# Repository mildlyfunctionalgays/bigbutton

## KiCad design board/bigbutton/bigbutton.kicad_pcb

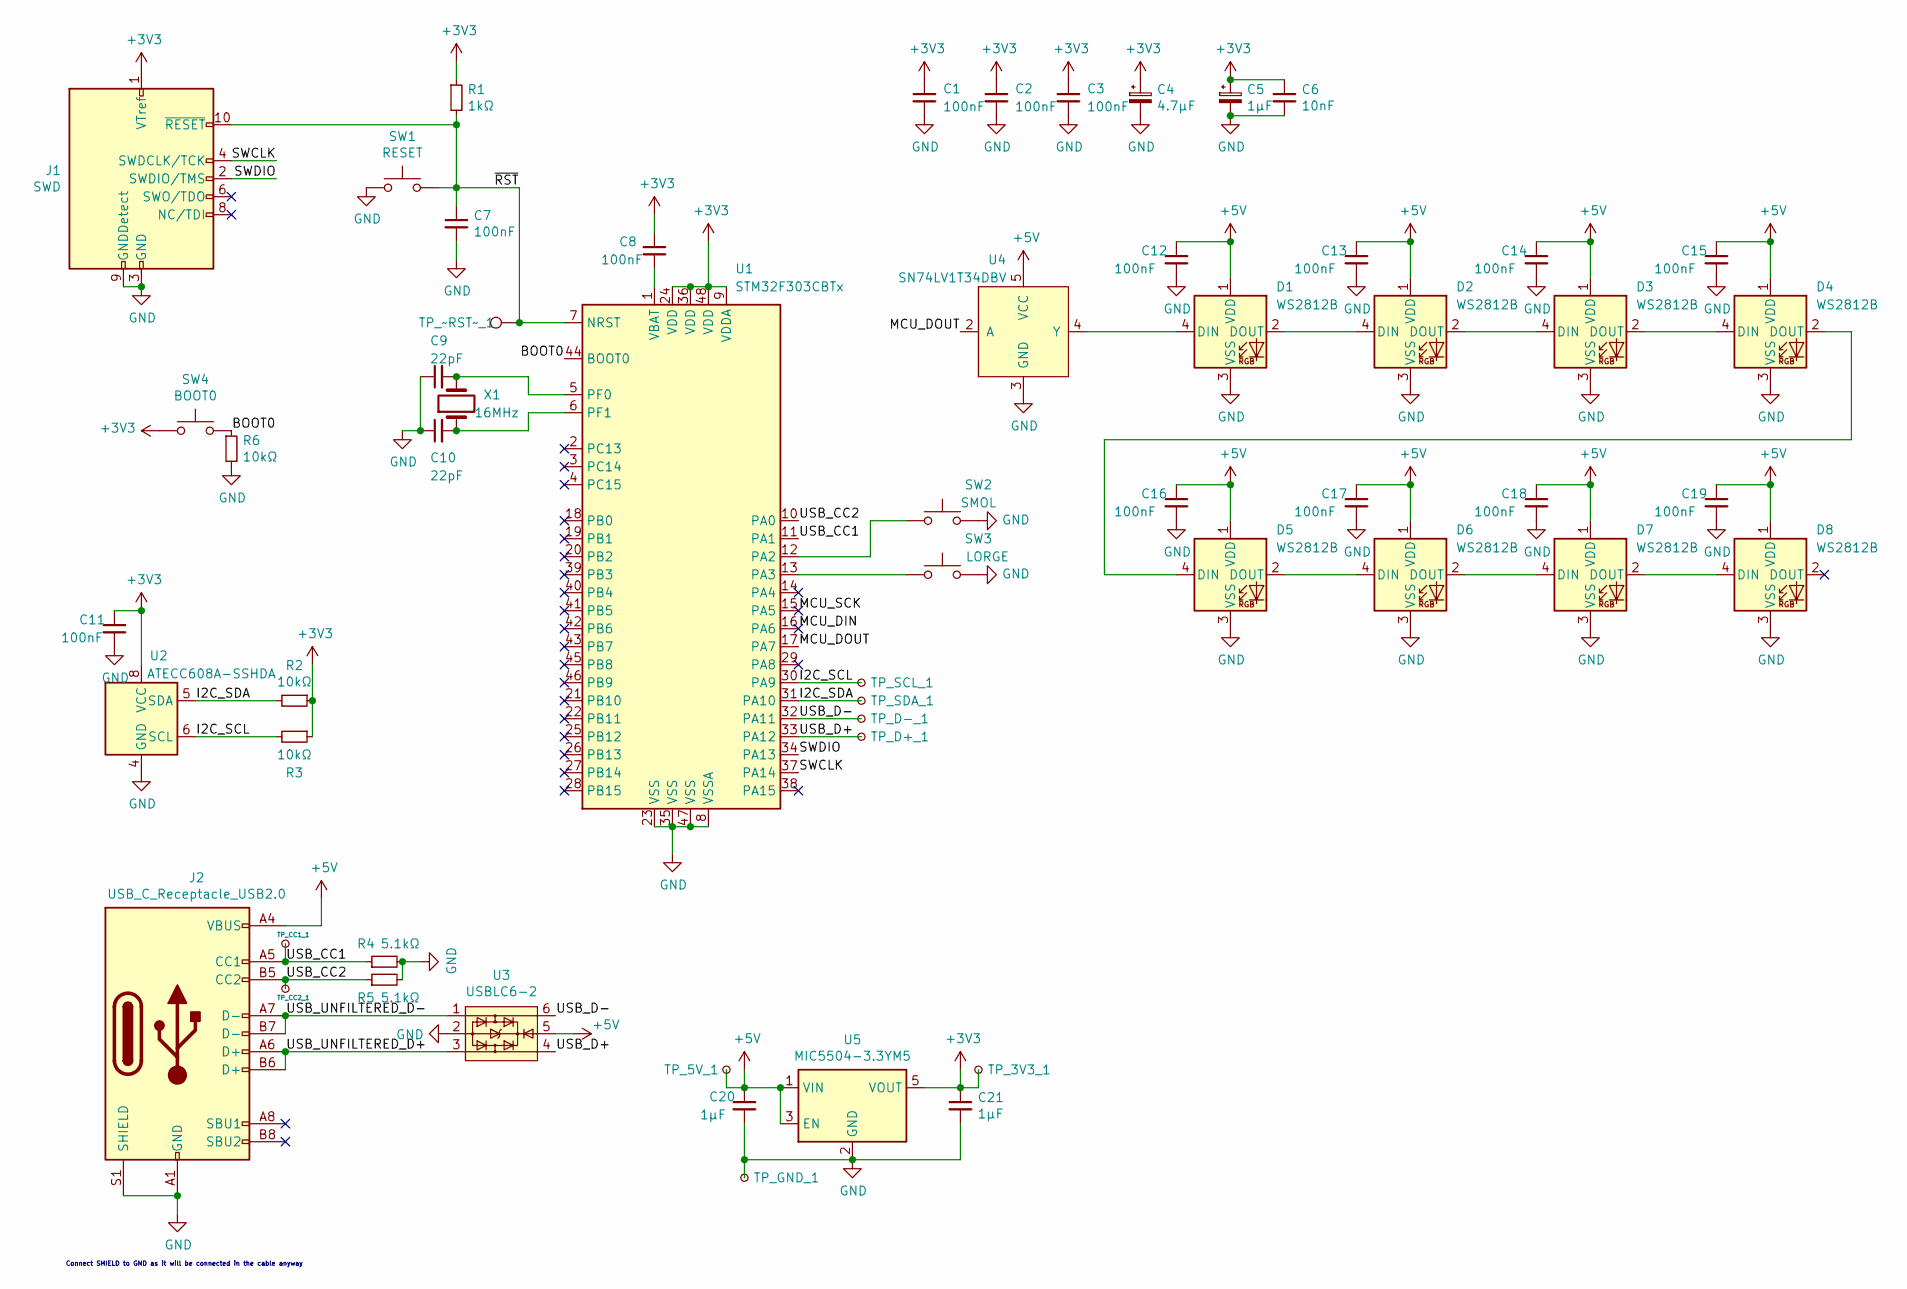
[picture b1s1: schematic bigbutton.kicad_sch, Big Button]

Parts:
C1, C2, C3, C7, C8, C11, C12, C13, C14, C15, C16, C17, C18, C19: 100nF; C_0603_1608Metric
C4: 4.7µF; C_0603_1608Metric
C5, C20, C21: 1µF; C_0603_1608Metric
C6: 10nF; C_0603_1608Metric
C9, C10: 22pF; C_0603_1608Metric
D1, D2, D3, D4, D5, D6, D7, D8: WS2812B; LED_WS2812B_PLCC4_5.0x5.0mm_P3.2mm
J1: SWD; PinHeader_2x05_P1.27mm_Vertical
J2: USB_C_Receptacle_USB2.0; USB_C_Receptacle_JING_C167321_HandSolder
R1: 1kΩ; R_0603_1608Metric
R2, R3, R6: 10kΩ; R_0603_1608Metric
R4, R5: 5.1kΩ; R_0603_1608Metric
SW1: RESET; SW_SPST_XKB_TS-1187A
SW2: SMOL; SW_Cherry_MX_1.00u_PCB
SW3: LORGE; SW_BIG_SWITCH
SW4: BOOT0; SW_SPST_XKB_TS-1187A
TP_3V3_1, TP_5V_1: TestPoint_Small; TestPoint_Pad_D1.0mm
TP_CC1_1: TP_CC1; TestPoint_Pad_D1.0mm
TP_CC2_1: TP_CC2; TestPoint_Pad_D1.0mm
TP_D+_1: TestPoint_Small; TestPoint_Pad_D1.0mm
TP_D-_1: TestPoint_Small; TestPoint_Pad_D1.0mm
TP_GND_1: TestPoint_Small; TestPoint_Pad_D1.0mm
TP_SCL_1: TestPoint_Small; TestPoint_Pad_D1.0mm
TP_SDA_1: TestPoint_Small; TestPoint_Pad_D1.0mm
TP_~RST~_1: TestPoint; TestPoint_Pad_D1.0mm
U1: STM32F303CBTx; LQFP-48_7x7mm_P0.5mm
U2: ATECC608A-SSHDA; SOIC-8_3.9x4.9mm_P1.27mm
U3: USBLC6-2; SOT-23-6_Handsoldering
U4: SN74LV1T34DBV; SOT-23-5_HandSoldering
U5: MIC5504-3.3YM5; SOT-23-5_HandSoldering
X1: 16MHz; Resonator-2Pin_W10.0mm_H5.0mm

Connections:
+3V3: C1.1, C2.1, C3.1, C4.1, C5.1, C6.1, C8.1, C11.1, C21.1, J1.1 (VTref), R1.1, R2.1, R3.1, SW4.1, TP_3V3_1.1, U1.9 (VDDA), U1.24 (VDD), U1.36 (VDD), U1.48 (VDD), U2.8 (VCC), U5.5 (VOUT)
+5V: C12.1, C13.1, C14.1, C15.1, C16.1, C17.1, C18.1, C19.1, C20.1, D1.1 (VDD), D2.1 (VDD), D3.1 (VDD), D4.1 (VDD), D5.1 (VDD), D6.1 (VDD), D7.1 (VDD), D8.1 (VDD), J2.A4 (VBUS), J2.A9 (VBUS), J2.B4 (VBUS), J2.B9 (VBUS), TP_5V_1.1, U3.5, U4.5 (VCC), U5.1 (VIN), U5.3 (EN)
/BOOT0: R6.1, SW4.2, U1.44 (BOOT0)
/I2C_SCL: R3.2, TP_SCL_1.1, U1.30 (PA9), U2.6 (SCL)
/I2C_SDA: R2.2, TP_SDA_1.1, U1.31 (PA10), U2.5 (SDA)
/MCU_DIN: U1.16 (PA6)
/MCU_DOUT: U1.17 (PA7), U4.2 (A)
/MCU_SCK: U1.15 (PA5)
/SWCLK: J1.4 (SWDCLK/TCK), U1.37 (PA14)
/SWDIO: J1.2 (SWDIO/TMS), U1.34 (PA13)
/USB_CC1: J2.A5 (CC1), R4.1, TP_CC1_1.1, U1.11 (PA1)
/USB_CC2: J2.B5 (CC2), R5.1, TP_CC2_1.1, U1.10 (PA0)
/USB_D+: TP_D+_1.1, U1.33 (PA12), U3.4
/USB_D-: TP_D-_1.1, U1.32 (PA11), U3.6
/USB_UNFILTERED_D+: J2.A6 (D+), J2.B6 (D+), U3.3
/USB_UNFILTERED_D-: J2.A7 (D-), J2.B7 (D-), U3.1
/~RST: C7.1, J1.10 (~RESET~), R1.2, SW1.2, TP_~RST~_1.1, U1.7 (NRST)
GND: C1.2, C2.2, C3.2, C4.2, C5.2, C6.2, C7.2, C9.1, C10.1, C11.2, C12.2, C13.2, C14.2, C15.2, C16.2, C17.2, C18.2, C19.2, C20.2, C21.2, D1.3 (VSS), D2.3 (VSS), D3.3 (VSS), D4.3 (VSS), D5.3 (VSS), D6.3 (VSS), D7.3 (VSS), D8.3 (VSS), J1.3 (GND), J1.5 (GND), J1.9 (GNDDetect), J2.A1 (GND), J2.A12 (GND), J2.B1 (GND), J2.B12 (GND), J2.S1 (SHIELD), R4.2, R5.2, R6.2, SW1.1, SW2.2, SW3.2, TP_GND_1.1, U1.8 (VSSA), U1.23 (VSS), U1.35 (VSS), U1.47 (VSS), U2.4 (GND), U3.2, U4.3 (GND), U5.2 (GND)
unnamed: C8.2, U1.1 (VBAT)
unnamed: C9.2, U1.5 (PF0), X1.2
unnamed: C10.2, U1.6 (PF1), X1.1
unnamed: D1.2 (DOUT), D2.4 (DIN)
unnamed: D1.4 (DIN), U4.4 (Y)
unnamed: D2.2 (DOUT), D3.4 (DIN)
unnamed: D3.2 (DOUT), D4.4 (DIN)
unnamed: D4.2 (DOUT), D5.4 (DIN)
unnamed: D5.2 (DOUT), D6.4 (DIN)
unnamed: D6.2 (DOUT), D7.4 (DIN)
unnamed: D7.2 (DOUT), D8.4 (DIN)
unnamed: SW2.1, U1.12 (PA2)
unnamed: SW3.1, U1.13 (PA3)

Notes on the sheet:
Connect SHIELD to GND as it will be connected in the cable anyway

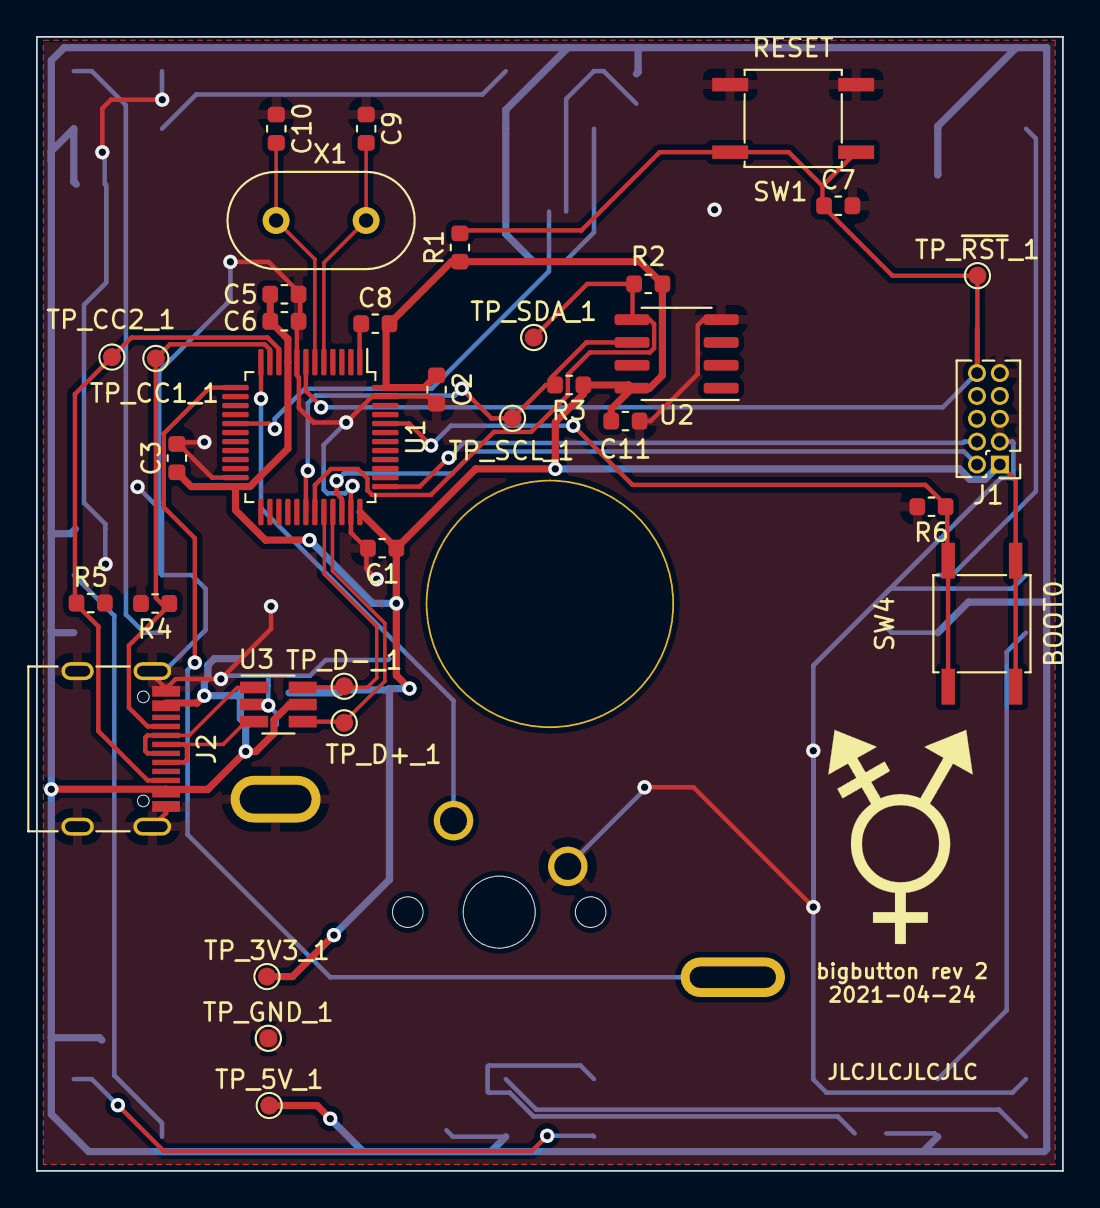
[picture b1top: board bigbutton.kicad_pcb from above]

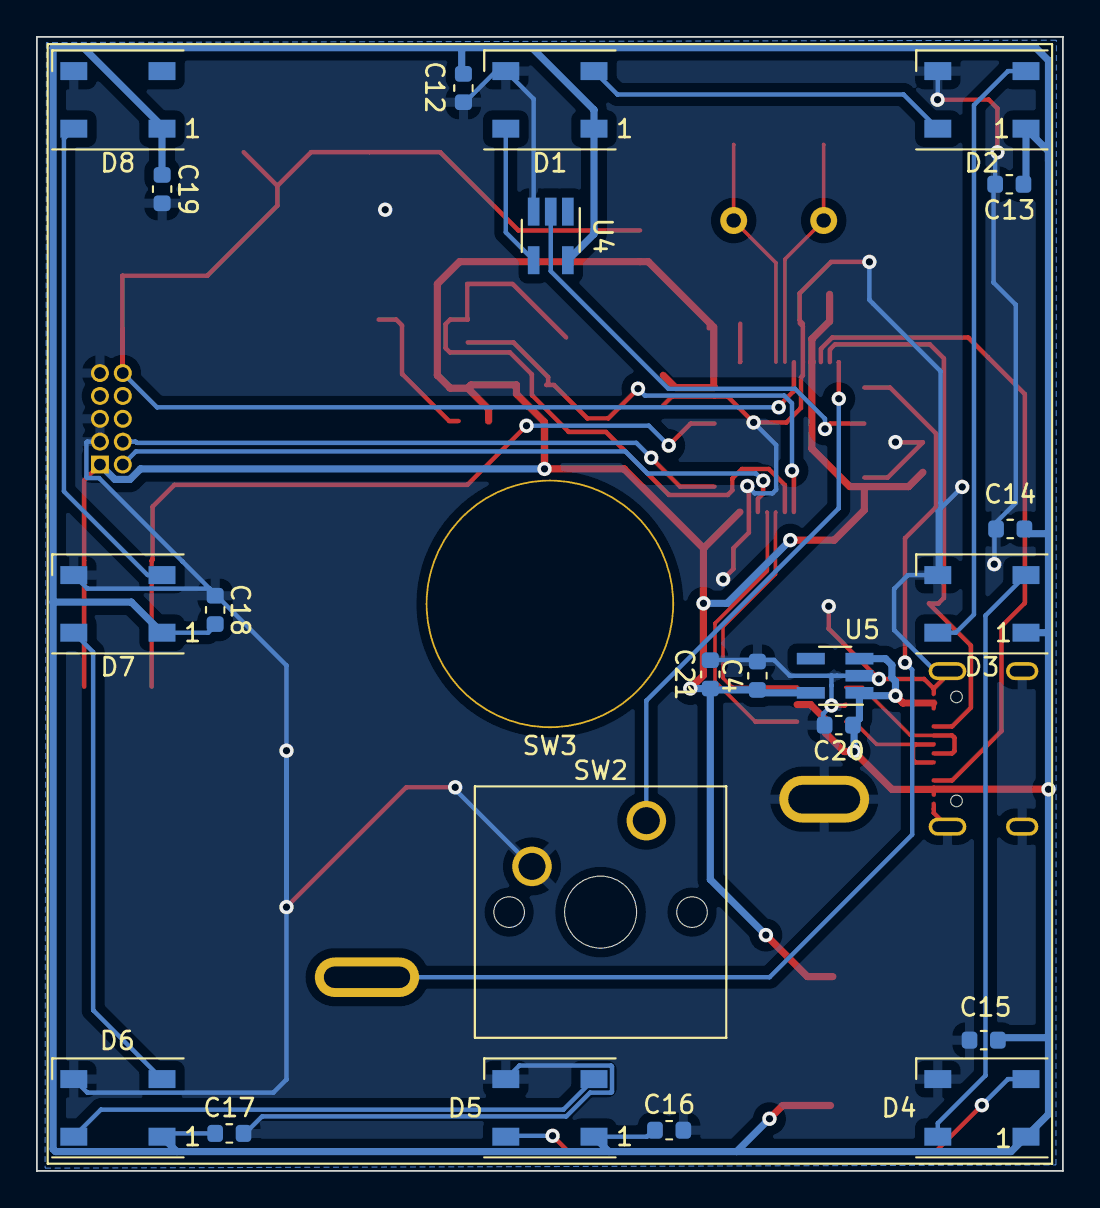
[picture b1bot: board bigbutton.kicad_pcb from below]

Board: 2 copper layers, 57.0 x 63.0 mm, 58 parts (23 on the bottom side), 29 nets.

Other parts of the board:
G0: LOGO; trans

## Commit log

2020-09-14 Start PCB
2020-09-15 Start moving to STM32
2020-09-16 Add LEDs and create a symbol for level shifter
2020-09-16 Add vreg
2020-09-25 Start PCB routing
2020-09-25 Done with first routing attempt
2020-09-26 Lots of rerouting
2020-09-26 Further rerouting
2020-09-26 Add BOOT0 button
2020-09-26 Clean up silkscreen
2020-09-26 Send for production (rev. 1)
2020-09-27 Switch to pin-compatible STM32F303CBT6, as reflected in order
2020-10-10 Switch to a top-mount USB connector from an incorrect mid-mount
2020-10-10 Adjust board, add trans symbol to silkscreen
2020-10-18 Update footprint for bigbutton
2021-04-24 Hopefully revision 2
2021-04-25 Add gerbers
2021-04-25 Migrate to new library format
2021-04-26 Add SK6812 Mini E symbol and footprint
